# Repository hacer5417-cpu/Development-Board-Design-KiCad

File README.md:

# STM32 Development Board Design 

An open-source, custom STM32 microcontroller development board designed from scratch using **KiCad**. This project covers the entire hardware development lifecycle, including schematic capture, component selection, power management design, two-layer PCB layout routing, and 3D visualization.

---

## Hardware Gallery & Visuals

### 1. Schematic Design & Architecture

*Clean and structured schematic diagram featuring the STM32 microcontroller pinouts, crystal oscillators, decoupling capacitors, peripheral interfaces, and voltage regulation circuit.*

### 2. 3D Model View (Top Side)

*3D rendering of the populated top side, showcasing component alignments, RGB status LED, push buttons, micro-USB interface, and peripheral headers.*

### 3. 3D Model View (Bottom Side)

*3D rendering of the bottom side, featuring the power management component placement, ground planes, and custom silkscreen branding.*

---

## Technical Specifications & Features

* **EDA Tool:** KiCad (Schematic Capture & PCB Layout)
* **Microcontroller:** STM32 Series (LQFP-48 Package)
* **Power Management:** On-board low-dropout (LDO) voltage regulator circuit with proper filtering capacitors for stable operation.
* **Signal Integrity:** Designed with short return paths, clear ground plane separation, and optimized routing for high-frequency (HSE) and low-frequency (LSE) crystal oscillators.
* **UI & Peripherals:** Integrated Reset/User buttons, an RGB LED indicator, boot mode configuration jumpers, and easily accessible breakout headers for all GPIOs.
* **Aesthetics:** Custom silkscreen layer layout featuring personalized branding.

---

## Future Enhancements
* Automated hardware validation and basic firmware testing (Blinky, UART communication).
* Designing an external enclosure model using CAD tools.

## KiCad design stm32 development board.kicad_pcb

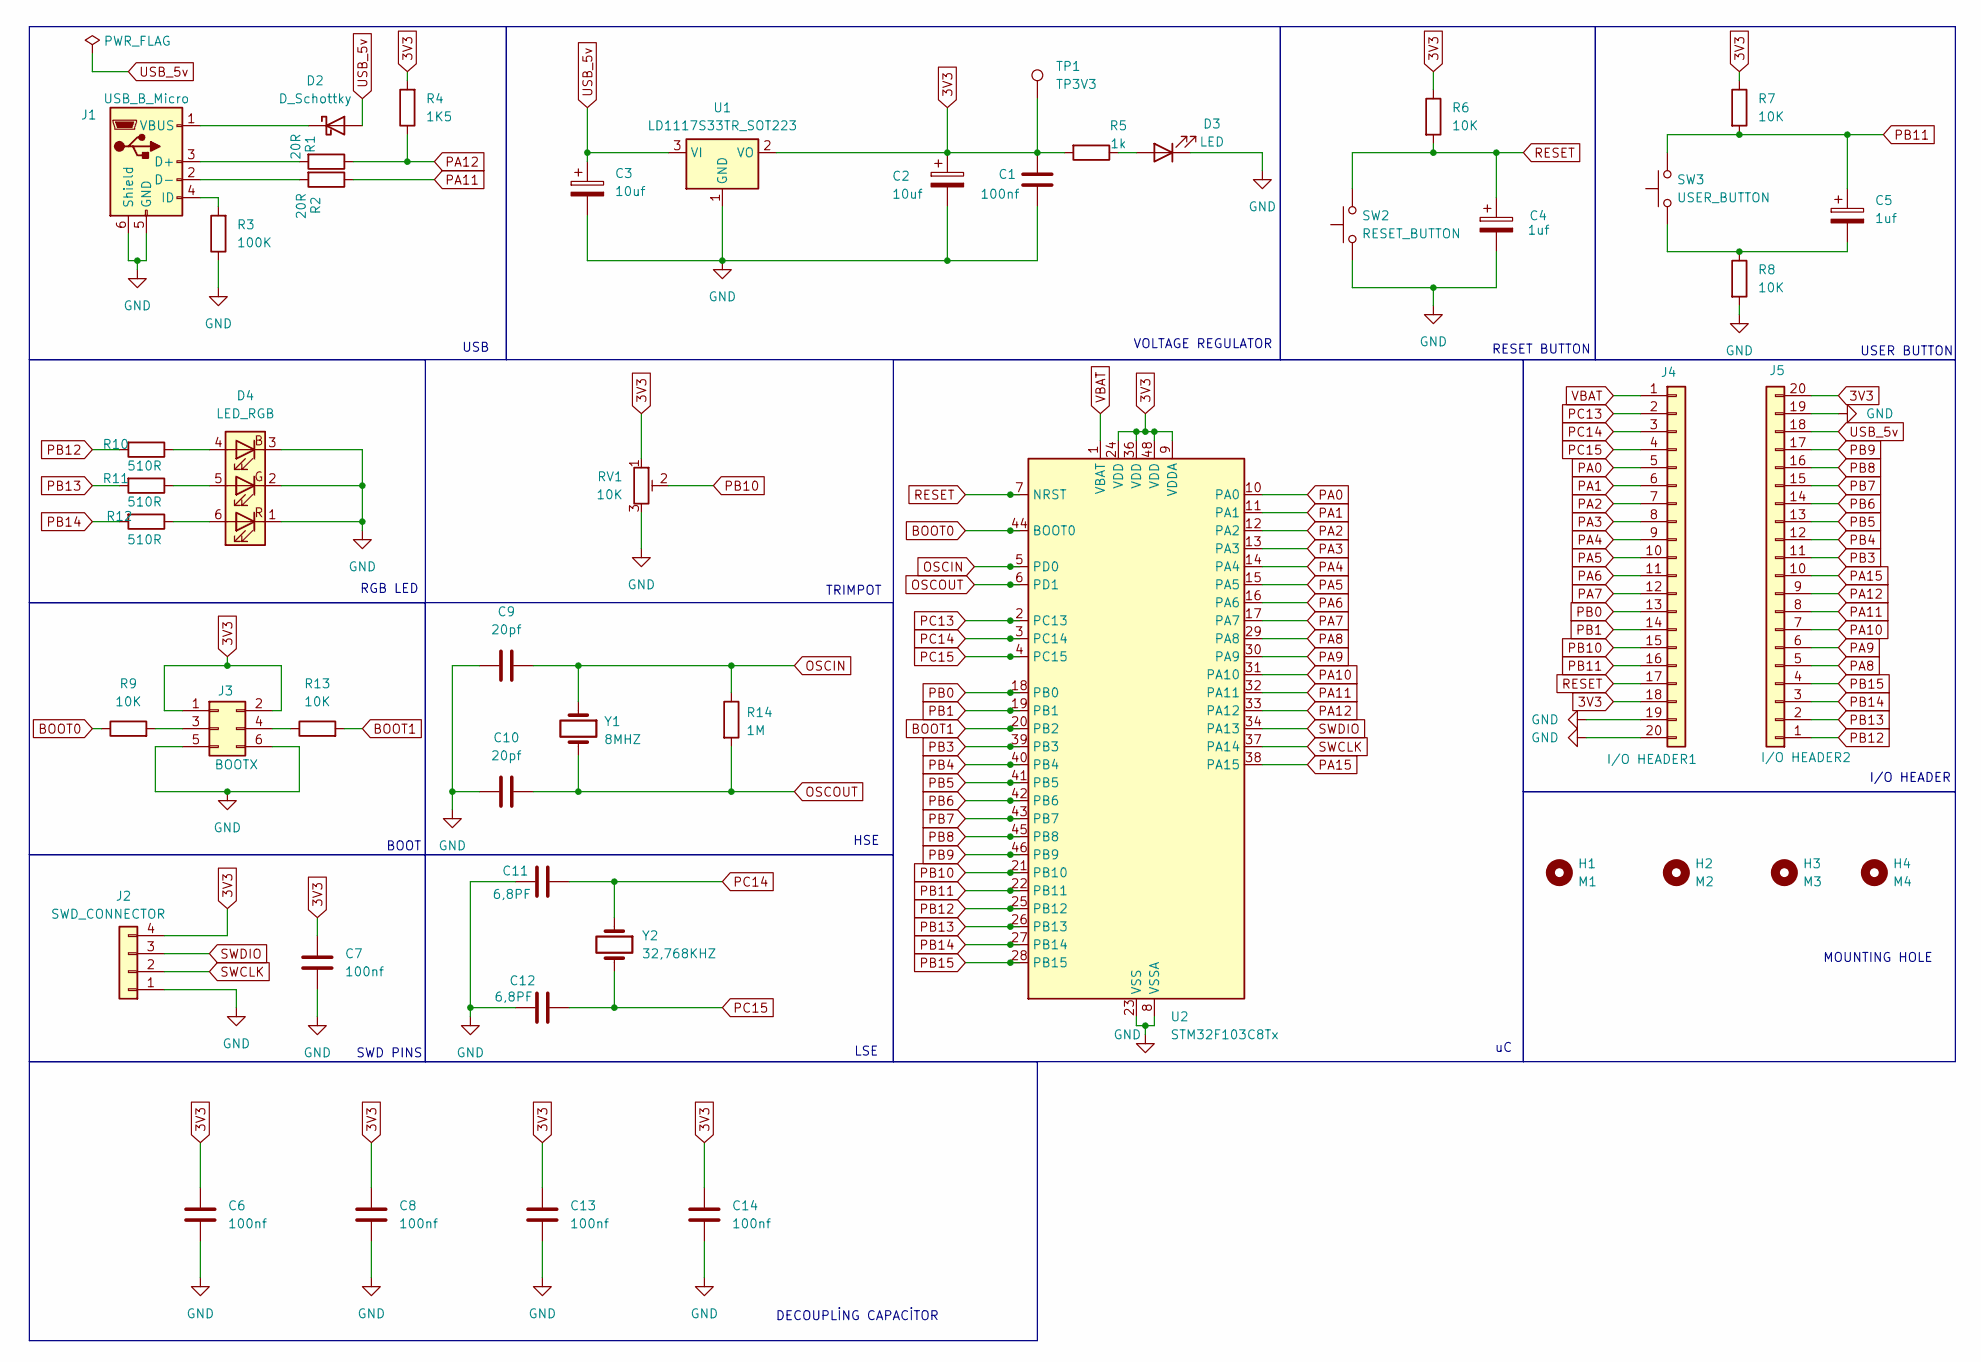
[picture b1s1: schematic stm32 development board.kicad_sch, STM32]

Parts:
C1, C6, C7, C8, C13, C14: 100nf; C_0603_1608Metric
C2, C3: 10uf; CP_EIA-1608-08_AVX-J
C4, C5: 1uf; CP_EIA-1608-08_AVX-J
C9, C10: 20pf; C_0603_1608Metric
C11, C12: 6,8PF; C_0603_1608Metric
D2: D_Schottky; D_TUMD2
D3: LED; LED_0805_2012Metric
D4: LED_RGB; LED_RGB_5050-6
H1: M1; MountingHole_2.2mm_M2_Pad_Via
H2: M2; MountingHole_2.2mm_M2_Pad_Via
H3: M3; MountingHole_2.2mm_M2_Pad_Via
H4: M4; MountingHole_2.2mm_M2_Pad_Via
J1: USB_B_Micro; USB_Micro-B_Molex_47346-0001
J2: SWD_CONNECTOR; PinHeader_1x04_P2.54mm_Horizontal
J3: BOOTX; PinHeader_2x03_P2.54mm_Vertical
J4: I/O HEADER1; PinHeader_1x20_P2.54mm_Vertical
J5: I/O HEADER2; PinHeader_1x20_P2.54mm_Vertical
R1, R2: 20R; R_0603_1608Metric
R3: 100K; R_0603_1608Metric
R4: 1K5; R_0603_1608Metric
R5: 1k; R_0603_1608Metric
R6, R7, R8, R9, R13: 10K; R_0603_1608Metric
R10, R11, R12: 510R; R_0603_1608Metric
R14: 1M; R_0603_1608Metric
RV1: 10K; Potentiometer_Bourns_3314G_Vertical
SW2: RESET_BUTTON; SW_SPST_B3U-1000P
SW3: USER_BUTTON; SW_PUSH_6mm_H8mm
TP1: TP3V3; TestPoint_Pad_D1.0mm
U1: LD1117S33TR_SOT223; SOT-223-3_TabPin2
U2: STM32F103C8Tx; LQFP-48_7x7mm_P0.5mm
Y1: 8MHZ; Crystal_HC49-4H_Vertical
Y2: 32,768KHZ; Crystal_C26-LF_D2.1mm_L6.5mm_Horizontal

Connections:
3V3: C1.1, C2.1, C6.1, C7.1, C8.1, C13.1, C14.1, J2.4, J3.1, J3.2, J4.18, J5.20, R4.2, R5.2, R6.1, R7.1, RV1.1, TP1.1, U1.2 (VO), U2.9 (VDDA), U2.24 (VDD), U2.36 (VDD), U2.48 (VDD)
BOOT0: R9.1, U2.44 (BOOT0)
BOOT1: R13.2, U2.20 (PB2)
GND: C1.2, C2.2, C3.2, C4.2, C6.2, C7.2, C8.2, C9.1, C10.1, C11.1, C12.1, C13.2, C14.2, D3.1 (K), D4.1 (RK), D4.2 (GK), D4.3 (BK), J1.5 (GND), J1.6 (Shield), J2.1, J3.5, J3.6, J4.19, J4.20, J5.19, R3.1, R8.2, RV1.3, SW2.1, U1.1 (GND), U2.8 (VSSA), U2.23 (VSS), U2.35 (VSS), U2.47 (VSS)
unnamed: C5.2, R8.1, SW3.1
unnamed: D2.1 (K), J1.1 (VBUS)
unnamed: D3.2 (A), R5.1
unnamed: D4.4 (BA), R10.1
unnamed: D4.5 (GA), R11.1
unnamed: D4.6 (RA), R12.1
unnamed: J1.3 (D+), R1.2
unnamed: J1.2 (D-), R2.2
unnamed: J1.4 (ID), R3.2
unnamed: J3.3, R9.2
unnamed: J3.4, R13.1
OSCIN: C9.2, R14.1, U2.5 (PD0), Y1.1
OSCOUT: C10.2, R14.2, U2.6 (PD1), Y1.2
PA0: J4.5, U2.10 (PA0)
PA1: J4.6, U2.11 (PA1)
PA2: J4.7, U2.12 (PA2)
PA3: J4.8, U2.13 (PA3)
PA4: J4.9, U2.14 (PA4)
PA5: J4.10, U2.15 (PA5)
PA6: J4.11, U2.16 (PA6)
PA7: J4.12, U2.17 (PA7)
PA8: J5.5, U2.29 (PA8)
PA9: J5.6, U2.30 (PA9)
PA10: J5.7, U2.31 (PA10)
PA11: J5.8, R2.1, U2.32 (PA11)
PA12: J5.9, R1.1, R4.1, U2.33 (PA12)
PA15: J5.10, U2.38 (PA15)
PB0: J4.13, U2.18 (PB0)
PB1: J4.14, U2.19 (PB1)
PB3: J5.11, U2.39 (PB3)
PB4: J5.12, U2.40 (PB4)
PB5: J5.13, U2.41 (PB5)
PB6: J5.14, U2.42 (PB6)
PB7: J5.15, U2.43 (PB7)
PB8: J5.16, U2.45 (PB8)
PB9: J5.17, U2.46 (PB9)
PB10: J4.15, RV1.2, U2.21 (PB10)
PB11: C5.1, J4.16, R7.2, SW3.2, U2.22 (PB11)
PB12: J5.1, R10.2, U2.25 (PB12)
PB13: J5.2, R11.2, U2.26 (PB13)
PB14: J5.3, R12.2, U2.27 (PB14)
PB15: J5.4, U2.28 (PB15)
PC13: J4.2, U2.2 (PC13)
PC14: C11.2, J4.3, U2.3 (PC14), Y2.1
PC15: C12.2, J4.4, U2.4 (PC15), Y2.2
RESET: C4.1, J4.17, R6.2, SW2.2, U2.7 (NRST)
SWCLK: J2.2, U2.37 (PA14)
SWDIO: J2.3, U2.34 (PA13)
USB_5v: C3.1, D2.2 (A), J5.18, U1.3 (VI)
VBAT: J4.1, U2.1 (VBAT)

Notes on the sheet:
RGB LED
BOOT
HSE
VOLTAGE REGULATOR
SWD PINS
RESET BUTTON
TRIMPOT
DECOUPLİNG CAPACİTOR
LSE
I/O HEADER
MOUNTING HOLE
USB
USER BUTTON

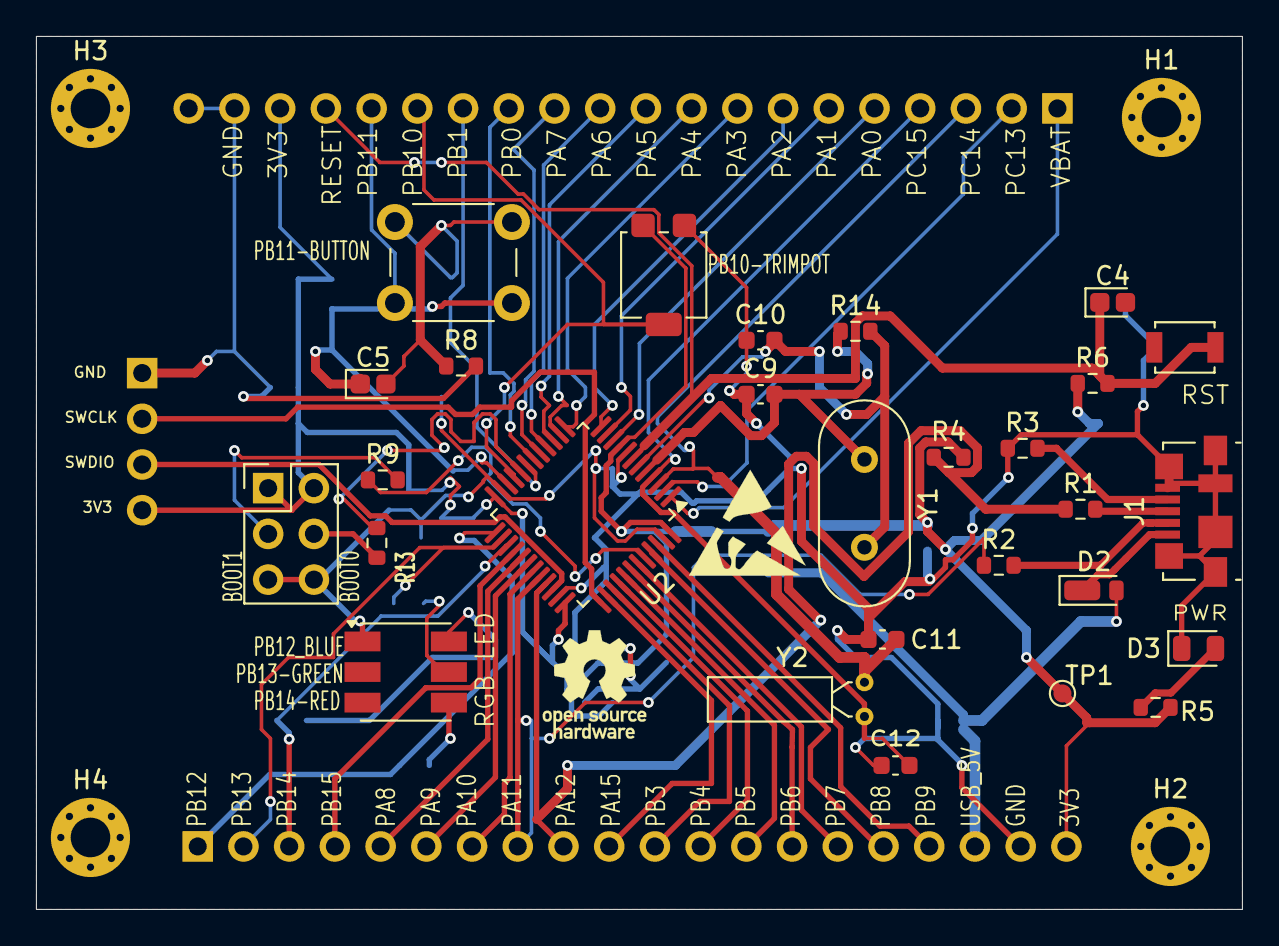
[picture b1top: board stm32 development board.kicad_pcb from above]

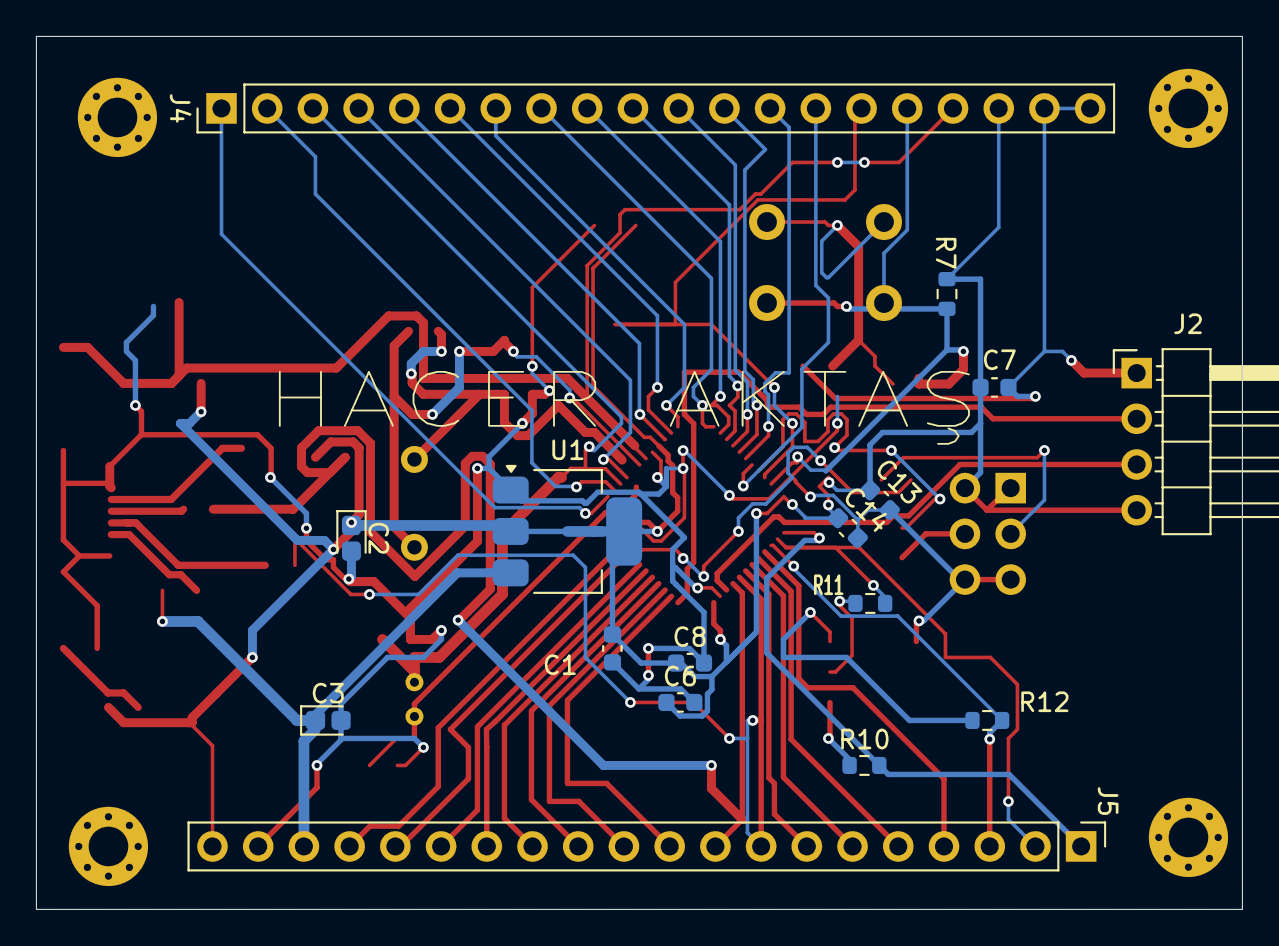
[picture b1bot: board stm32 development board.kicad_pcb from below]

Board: 2 copper layers, 67.0 x 48.5 mm, 48 parts (16 on the bottom side), 54 nets.
